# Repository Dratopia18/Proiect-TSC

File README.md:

# Proiect-TSC

# Diagrama Proiectului
<pre lang="markdown"> 
+-------------------------------------------+
|              POWER SECTION                |
|  +-------------+       +-----------------+|
|  | USB Type-C  |       | Charging Circuit||
|  | Connector   |------>| MCP73831        ||
|  | USB4110-GF-A|       | (Battery Mgmt)  ||
|  +-------------+       +-----------------+|
|         |                      |          |
|         v                      v          |
|  +-------------+       +-----------------+|
|  | USB to 3.3V |       | Battery Monitor ||
|  | XC6220A331MR|       | MAX17048G       ||
|  | (LDO Reg)   |       | (Fuel Gauge)    ||
|  +-------------+       +-----------------+|
|         |                                 |
+---------|---------------------------------+
          |
          v
+-----------------+        +-------------------+        +----------------+
| Interface       |        | Main Controller   |        | Memory         |
| +-------------+ |        | +---------------+ |        | +-----------+  |
| | microSD Card| |<------>| | ESP32-C6      | |<------>| | W25Q512J  |  |
| | Slot        | |        | | WROOM Module  | |        | | Flash     |  |
| +-------------+ |        | +---------------+ |        | | (64MB)    |  |
|                 |        |         |         |        |             |  |
| +-------------+ |        |         |         |        | +-----------+  |
| | FPC/FFC     | |<-------+         |         +------->| | DS3231    |  |
| | Connector   | |        |         |         |        | | RTC       |  |
| | (24-pin)    | |        |         v         |        | | w/Battery |  |
| +-------------+ |        | +---------------+ |        +----------------+
+-----------------+        | | Control Logic | |
                           | | Buttons       | |
                           | | (Reset/Boot)  | |
                           | +---------------+ |
                           +-------------------+
                                    |
                                    v
                           +-------------------+
                           | Peripherals       |
                           | +--------------+  |
                           | | BME680       |  |
                           | | Environment  |  |
                           | | Sensor (I2C) |  |
                           | +--------------+  |
                           |                   |
                           | +--------------+  |
                           | | QWIIC/I2C    |  |
                           | | Connector    |  |
                           | +--------------+  |
                           +-------------------+
</pre>

# Tabela BOM a proiectului
| Nr. | Componentă | Descriere | Furnizor | Link Achiziție | Datasheet |
|-----|------------|-----------|----------|----------------|-----------|
| 1 | ESP32-C6-WROOM-1-N8 | Microcontroller ESP32-C6 cu WiFi 6 și Bluetooth 5 | Digikey | https://www.digikey.com/en/products/detail/espressif-systems/ESP32-C6-WROOM-1-N8/17728866 | https://www.espressif.com/sites/default/files/documentation/esp32-c6-wroom-1_wroom-1u_datasheet_en.pdf |
| 2 | BME680 | Senzor integrat de mediu (temperatură, umiditate, presiune, gaz) | Digikey | https://www.digikey.com/en/products/detail/bosch-sensortec/BME680/7401317 | https://www.bosch-sensortec.com/media/boschsensortec/downloads/datasheets/bst-bme680-ds001.pdf |
| 3 | SD0805S020S1R0 | Diodă Schottky Barrier | Mouser | [https://www.mouser.com/ProductDetail/581-SD0805S020S1R0](https://ro.mouser.com/ProductDetail/KYOCERA-AVX/SD0805S020S1R0?qs=jCA%252BPfw4LHbpkAoSnwrdjw%3D%3D) | [http://datasheets.avx.com/schottky.pdf](https://ro.mouser.com/datasheet/2/40/schottky-3165252.pdf) |
| 4 | CPH3225A | Condensator 0.011F 3.3V 1210 | Digikey | https://www.digikey.com/en/products/detail/murata-electronics/CPH3225A/8692444 | [https://product.tdk.com/info/en/catalog/datasheets/mlcc_commercial_general_en.pdf](https://mm.digikey.com/Volume0/opasdata/d220001/medias/docus/6537/rev05-CPHCPM.pdf) |
| 5 | XC6220A331MR_G | Regulator de tensiune LDO | Digikey | https://www.digikey.com/en/products/detail/torex-semiconductor-ltd/XC6220A331MR-G/10165775 | https://www.torexsemi.com/file/xc6220/XC6220.pdf |
| 6 | SI1308EDL_T1_GE3 | Tranzistor MOSFET N-Channel | Digikey | https://www.digikey.com/en/products/detail/vishay-siliconix/SI1308EDL-T1-GE3/4876435 | https://www.vishay.com/docs/68734/si1308edl.pdf |
| 7 | CSR0402JTR470 | Rezistor 47 Ohm 0402 | Digikey | https://www.digikey.com/en/products/detail/stackpole-electronics-inc/CSR0402JTR470/6270526 | https://www.seielect.com/catalog/sei-rmcf_rmcp.pdf |
| 8 | KMS231GPLFS | Switch tactil | Mouser | [https://www.mouser.com/ProductDetail/611-KMS231GPLFS](https://ro.mouser.com/ProductDetail/CK/KMS231GP-LFS?qs=Qe4e1uPWiB2lCKabCZjjQg%3D%3D) | https://www.ckswitches.com/media/1464/kms.pdf |
| 9 | PGB1010603MR | Diodă de protecție ESD | Digikey | https://www.digikey.com/en/products/detail/littelfuse-inc/PGB1010603MR/715755 | https://www.littelfuse.com/~/media/electronics/datasheets/polymer_esd_suppressors/littelfuse_polymer_esd_suppressor_pgb_datasheet.pdf |
| 10 | CC0805KKX7R9BB105 | Condensator ceramic 1μF 50V | Digikey | https://www.digikey.com/en/products/detail/yageo/CC0805KKX7R9BB105/5195292 | https://www.yageo.com/upload/media/product/productsearch/datasheet/mlcc/UPY-GPHC_X7R_6.3V-to-50V_18.pdf |
| 11 | C1206C105K5RAC | Condensator ceramic 1μF 50V 1206 | Mouser | [https://www.mouser.com/ProductDetail/80-C1206C105K5R](https://ro.mouser.com/ProductDetail/KEMET/C1206C105K5RAC?qs=NTAB53G5bVDYFBtoIe7UwQ%3D%3D) | https://www.yageo.com/upload/media/product/productsearch/datasheet/mlcc/UPY-GPHC_X7R_6.3V-to-50V_18.pdf |
| 12 | C0402C105Z9VACTU | Condensator ceramic 1μF 10V 0402 | Mouser | [https://www.mouser.com/ProductDetail/80-C0402C105Z9VAC](https://ro.mouser.com/ProductDetail/KEMET/C0402C105Z9VACTU?qs=gt1LBUVyoHlQieoJt4iw1w%3D%3D) | https://www.yageo.com/upload/media/product/productsearch/datasheet/mlcc/UPY-GPHC_X5R_4V-to-50V_25.pdf |
| 13 | TAJB107K010RNJ | Condensator tantalum 100μF 10V | Digikey | https://www.digikey.com/en/products/detail/kyocera-avx/TAJB107K010RNJ/9748493 | https://componentsearchengine.com/Datasheets/1/TAJB107K010RNJ.pdf |
| 14 | C0402C475M9PACTU | Condensator ceramic 4.7μF 6.3V 0402 | Mouser | [https://www.mouser.com/ProductDetail/80-C0402C475M9PAC](https://ro.mouser.com/ProductDetail/KEMET/C0402C475M9PACTU?qs=x4XeXhDQKnr0GX0Xu9DUoQ%3D%3D) | https://www.yageo.com/upload/media/product/productsearch/datasheet/mlcc/UPY-GPHC_Y5V_6.3V-to-50V_20.pdf |
| 15 | DMG2305UX_7 | Tranzistor MOSFET P-Channel | Digikey | https://www.digikey.com/en/products/detail/diodes-incorporated/DMG2305UX-7/4340667 | https://www.diodes.com/assets/Datasheets/DMG2305UX.pdf |
| 16 | WCR0402-100KFA | Rezistor 100k Ohm 0402 | Mouser | [https://www.mouser.com/ProductDetail/652-WCR0402-100KFA](https://ro.mouser.com/ProductDetail/Welwyn-Components-TT-Electronics/WCR0402-100KFA?qs=%2F5Ar%2FAxv93DcWIrqMX6zjw%3D%3D) | https://www.welwyn-tt.com/wp-content/uploads/2020/07/Welwyn_WCR_Series_-_Issue_5_-_April_2020.pdf |
| 17 | PFMF.050.2 | Siguranță PTC resetabilă | Mouser | [https://www.mouser.com/ProductDetail/652-PFMF.050.2](https://ro.mouser.com/ProductDetail/Schurter/PFMF.050.2?qs=1auRipcfynCums5v1iucSA%3D%3D) | https://www.littelfuse.com/~/media/electronics/datasheets/resettable_ptcs/littelfuse_ptc_pfmf_datasheet.pdf |
| 18 | 744043680 | Inductor de putere 68μH | Mouser | [https://www.mouser.com/ProductDetail/710-744043680](https://ro.mouser.com/ProductDetail/Wurth-Elektronik/744043680?qs=PGXP4M47uW6VkZq%252BkzjrHA%3D%3D) | https://www.we-online.com/components/products/datasheet/744043680.pdf |
| 19 | MBR0530T3G | Diodă Schottky 0.5A 30V | Mouser | [https://www.mouser.com/ProductDetail/863-MBR0530T3G](https://ro.mouser.com/ProductDetail/onsemi/MBR0530T3G?qs=3JMERSakebpEmdUS6GetdQ%3D%3D) | https://www.onsemi.com/pdf/datasheet/mbr0530t1-d.pdf |
| 20 | SM04B_SRSS_TB | Conector JST SH 4 pini SMD | Digikey | https://www.digikey.com/en/products/detail/jst-sales-america-inc/SM04B-SRSS-TB-LF-SN/926710 | https://www.jst-mfg.com/product/pdf/eng/eSH.pdf |
| 21 | MAX17048G_T10 | Monitor de baterie Li+ | Digikey | https://www.digikey.com/en/products/detail/analog-devices-inc-maxim-integrated/MAX17048G-T10/3758921 | https://datasheets.maximintegrated.com/en/ds/MAX17048-MAX17049.pdf |
| 22 | MCP73831T_2ACI_OT | Controller de încărcare Li-Ion/Li-Polymer | Digikey | https://www.digikey.com/en/products/detail/microchip-technology/MCP73831T-2ACI-OT/964301 | https://ww1.microchip.com/downloads/en/DeviceDoc/MCP73831-Family-Data-Sheet-DS20001984H.pdf |
| 23 | BD5229G-TR | Detector de tensiune cu timp de întârziere ajustabil | Digikey | https://www.digikey.com/en/products/detail/rohm-semiconductor/BD5229G-TR/658502 | https://fscdn.rohm.com/en/products/databook/datasheet/ic/power/voltage_detector/bd52xxg-e.pdf |
| 24 | DS3231SN# | RTC (Real Time Clock) Serial | Digikey | https://www.digikey.com/en/products/detail/analog-devices-inc-maxim-integrated/DS3231SN/1197576 | https://datasheets.maximintegrated.com/en/ds/DS3231.pdf |
| 25 | W25Q512JVEIQ | Memorie Flash SPI 512Mbit | Digikey | https://www.digikey.com/en/products/detail/winbond-electronics/W25Q512JVEIQ/10244706 | https://www.winbond.com/resource-files/w25q512jv%20revf%2010142020%20plus.pdf |
| 26 | FH34SRJ-24S-0.5SH(99) | Conector FPC 24 pini | Mouser | [https://www.mouser.com/ProductDetail/798-FH34SRJ24S05SH99](https://ro.mouser.com/ProductDetail/Hirose-Connector/FH34SRJ-24S-0.5SH99?qs=vcbW%252B4%252BSTIpKBl5ap9J8Fw%3D%3D) | https://www.hirose.com/product/document?clcode=CL0570-0597-0-00&productname=FH34SRJ-24S-0.5SH(99)&series=FH34&documenttype=Catalog&lang=en&documentid=D31688_en |
| 27 | C0402C104K4RACTU | Condensator ceramic 0.1μF 16V 0402 | Digikey | https://www.digikey.com/en/products/detail/kyocera-avx/C0402C104K4RACTU/789653 | https://ds.yuden.co.jp/TYCOMPAS/ut/download?pn=CC0402JRNPO9BN220&fileType=CA |
| 28 | USBLC6-2SC6Y | Circuit de protecție ESD pentru USB | Digikey | https://www.digikey.com/en/products/detail/stmicroelectronics/USBLC6-2SC6Y/2819177 | https://www.st.com/resource/en/datasheet/usblc6-2.pdf |
| 29 | USB4110-GF-A | Conector USB Type-C | Digikey | https://www.digikey.com/en/products/detail/gct/USB4110-GF-A/10384547 | https://gct.co/connector/usb4110 |
| 30 | 112A-TAAR-R03 | Conector pentru antenă | Digikey | https://www.digikey.com/en/products/detail/linx-technologies-inc/112A-TAAR-R03/17633923 | https://linxtechnologies.com/wp/wp-content/uploads/112-series-data-sheet.pdf |

# Descrierea Funcționalității Hardware

## Modulul Microcontroller

Proiectul este bazat pe modulul ESP32-C6-WROOM-1-N8, un microcontroller de ultimă generație care include WiFi 6 și Bluetooth 5. Acest modul oferă performanțe excelente și un consum de energie redus, fiind ideal 
pentru aplicații IoT.

## Senzori

BME680 - un senzor integrat de mediu produs de Bosch Sensortec care măsoară:

* Temperatura (între -40°C și +85°C)
* Umiditatea relativă (între 0% și 100%)
* Presiunea barometrică (între 300hPa și 1100hPa)
* Calitatea aerului (prin măsurarea compușilor organici volatili)

Senzorul se conectează la ESP32-C6 prin interfața I2C, utilizând pinii SDA și SCL.

DS3231SN - un Real Time Clock (RTC) de înaltă precizie:

* Menține data și ora precisă
* Include compensare de temperatură
* Interfațare prin I2C
* Backup cu baterie pentru păstrarea timpului când alimentarea principală este întreruptă

## Sistemul de Alimentare

Încărcător de baterie Li-Ion/Li-Polymer:

* Controller dedicat MCP73831T-2ACI-OT
* LED indicator pentru starea încărcării
* Circuite de protecție pentru baterie

Management Energie:

* Regulator LDO XC6220A331MR_G pentru alimentare stabilă 3.3V
* Detector de tensiune BD5229G-TR pentru monitorizarea nivelului bateriei
* Monitor de baterie MAX17048G_T10 pentru măsurarea precisă a nivelului de încărcare
* Circuite de protecție PTC (PFMF.050.2) pentru protecție la supracurent

Convertoare DC-DC:
* Inductori de putere (744043680) pentru conversia eficientă a tensiunii
* Diode Schottky (SD0805S020S1R0, MBR0530T3G) pentru circuitele de comutație

## Stocare
Sistemul include memoria flash W25Q512JVEIQ de 512Mbit (64MB) conectată prin interfața SPI, oferind:

* Spațiu amplu pentru logging de date
* Viteză mare de citire/scriere (până la 104 MHz în mod SPI)
* Suport pentru modul Quad SPI pentru transfer de date accelerat
* Durată de retenție a datelor de peste 20 de ani

## Conectivitate

USB Type-C:

* Conector USB4110-GF-A pentru încărcare și comunicare
* Circuit de protecție USBLC6-2SC6Y pentru protecție ESD
* Suport pentru comunicare serială prin UART

Interfață FPC:

* Conector FH34SRJ-24S-0.5SH(99) cu 24 de pini
* Permite conectarea modulelor de expansiune sau a ecranelor
* Accesează multiple interfețe (I2C, SPI, GPIO)

Conectivitate Wireless:

* WiFi 6 integrat în modulul ESP32-C6
* Bluetooth 5.0 pentru conectivitate la dispozitive mobile
* Conector pentru antenă externă 112A-TAAR-R03 pentru îmbunătățirea recepției

## Interfața Utilizator

Butoane Tactile:

* Buton de boot (KMS231GPLFS) pentru intrarea în modul de programare
* Buton de reset (KMS231GPLFS) pentru repornirea sistemului
* Butoane adiționale configurabile de utilizator

LED-uri de Status:

* LED pentru indicarea stării de încărcare
* LED pentru indicarea activității sistemului
* LED-uri configurabile pentru notificări personalizate

# Pinii ESP32-C6: Functia si utilizarea fiecarui pin

| Pin     | Funcție        | Modul de utilizare                                               |
|---------|----------------|------------------------------------------------------------------|
| 3V3     | Supply         | Furnizează tensiune de 3.3V pentru componente.                   |
| GND     | Ground         | Referință pentru circuit.                                        |
| EN      | Enable         | Permite pornirea/resetarea modulului (tensiune ridicată = activ).|
| IO0     | INT_RTC (Interrupt)       | Pentru notificări, conectat la modulul RTC.                      |
| IO1     | RTC CLK        | Semnal de ceas pentru modulul RTC.                               |
| IO2     | SPI MISO       | Primire date de la periferice conectate prin SPI.                |
| IO3     | Status         | Semnalizează starea de ocupare a display-ului.                   |
| IO4     | Slave Select   | Selectează cardul SD.                                            |
| IO5     | Data/Command   | Selectează între modul de date și comenzi.                       |
| IO6     | SPI CLK        | Semnal de ceas pentru SPI.                                       |
| IO7     | SPI MOSI       | Transfer date către periferice conectate prin SPI.               |
| IO8     | GPIO           | Pin general GPIO.                                                |
| IO9     | IO/BOOT           | Conectat la un buton pentru intrarea în modul de boot.           |
| IO10    | EPD_CS  (Chip Select)    | Activează comunicarea cu display-ul.                             |
| IO11    | FLASH_CS (Chip Select)    | Activează comunicarea cu memoria flash.                          |
| IO12    | USB_D-         | Pentru USB.                                                      |
| IO13    | USB_D+         | Pentru USB.                                                      |
| IO15    | IO/CHANGE         | Conectat la un buton.                                            |
| IO16    | TX             | Pentru UART.                                                     |
| IO17    | RX             | Pentru UART.                                                     |
| IO18    | RTC_RST        | Pentru resetarea modulului RTC.                                  |
| IO19    | I2C_PW         | Supply pentru I2C.                                               |
| IO20    | EPD_3V3_C      | Alimentare display.                                              |
| IO21    | SDA            | Linia de date pentru I2C.                                        |
| IO22    | SCL            | Semnalul de ceas pentru I2C.                                     |
| IO23    | EPD_RST        | Pentru resetarea display-ului.                                   |

## Calcule de Consum Energetic

Consumul în diferite moduri de operare:

Mod Activ (Toate funcțiile active):

* ESP32-C6: ~60mA @ 3.3V
* BME680: ~3.7mA în mod activ
* DS3231: ~0.15mA
* Memorie Flash: ~15mA în operație de scriere
* Monitor baterie: ~0.5mA
* Circuite adiționale: ~5mA

Total mod activ: ~84.35mA @ 3.3V = 278.35mW

Mod Normal (Funcționare tipică):

* ESP32-C6: ~35mA (WiFi activ, procesor la viteză medie)
* BME680: ~1mA (măsurători periodice)
* DS3231: ~0.15mA
* Memorie Flash: ~1mA (operații ocazionale)
* Circuite adiționale: ~3mA

Total mod normal: ~40.15mA @ 3.3V = 132.5mW

Mod Sleep (Economisire energie):

* ESP32-C6: ~10μA (deep sleep)
* BME680: ~0.15μA (sleep)
* DS3231: ~0.15mA (activ pentru menținerea timpului)
* Circuite adiționale: ~50μA

Total mod sleep: ~0.21mA @ 3.3V = 0.693mW

Durata de viață a bateriei:

Considerând o baterie Li-Po de 1200mAh:

* În mod activ: ~14.2 ore
* În mod normal: ~29.9 ore
* Cu ciclu de funcționare optimizat (10% mod normal, 90% mod sleep): ~8-10 zile

# Design PCB și Considerații Mecanice

Dimensiuni PCB:

* Dimensiuni totale: 80mm x 40mm
* Grosime PCB: 1 mm
* Straturi: 3 (Top, Dielectrical, Bottom)

Considerații Termice:

* Componentele cu disipare mare de căldură (regulatoare, încărcător baterie) plasate cu zone de disipare adecvate
* Vias termice sub ESP32-C6 pentru disiparea căldurii

Layout Componente:

* Secțiune RF (antenă WiFi/BT) izolată și optimizată pentru performanță
* Separarea circuitelor digitale de cele analogice pentru minimizarea interferențelor
* Componente sensibile la zgomot (senzori) plasate departe de surse de interferență
* Integrarea ESP32-C6 oferă capabilități WiFi 6 și Bluetooth de ultimă generație
* Senzorul BME680 permite monitorizarea completă a parametrilor de mediu
* Sistemul de management al energiei optimizat pentru durată lungă de funcționare
* Conectorul FPC permite extensibilitate și adăugarea de module viitoare

Perspective de dezvoltare:

* Adăugarea unui ecran E-Ink pentru afișare cu consum ultra-redus
* Implementarea unui încărcător solar pentru autonomie completă
* Dezvoltarea de module de expansiune specifice pentru diverse aplicații
* Optimizarea și mai pronunțată a consumului energetic pentru funcționare pe termen lung

Limitări actuale:

* Dimensiunile pot fi reduse în versiunile viitoare
* Costuri de producție pot fi optimizate prin reducerea numărului de componente
* Protecție IP limitată fără carcasă dedicată

# Concluzie
Proiectul actual reprezintă o platformă de dezvoltare IoT completă, bazată pe ESP32-C6, cu capabilități extinse de senzori, managementul energiei, și opțiuni de conectivitate. Design-ul hardware a fost realizat
cu accent pe eficiență energetică, flexibilitate și fiabilitate, permițând o gamă largă de aplicații de la monitorizarea mediului până la controlul automatizărilor.

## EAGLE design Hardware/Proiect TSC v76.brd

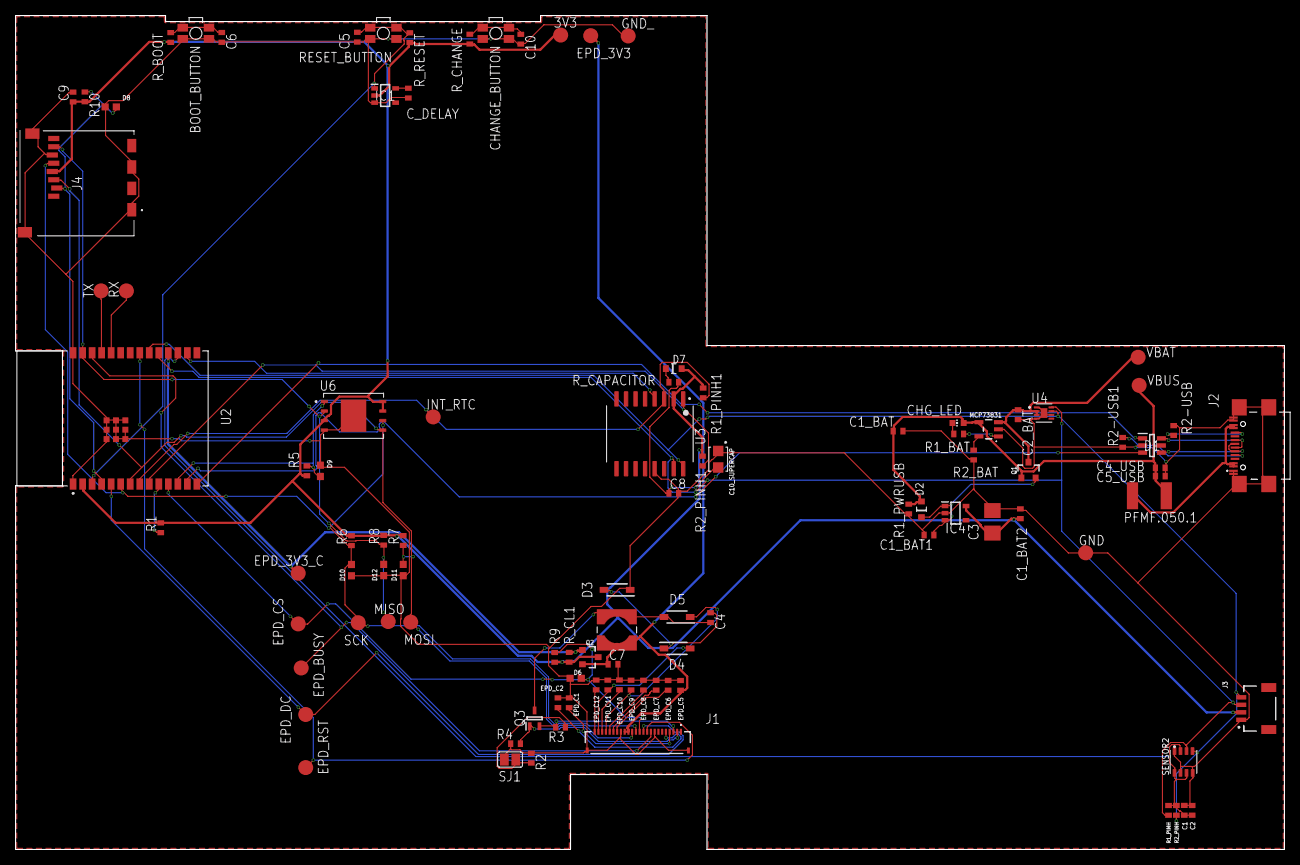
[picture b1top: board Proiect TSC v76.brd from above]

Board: 2 copper layers, 169.2 x 111.2 mm, 103 parts (0 on the bottom side), 55 nets.

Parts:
3V3: TPTP20R; TP20R
BOOT_BUTTON: BUTTON_CUSYOMV1; MYBUTTON
C1, C2, C4_USB, C5_USB, C9: 100nF; ESP32_WROVER_EAGLE-LTSPICE_C0402
C1_BAT, C1_BAT1, C1_BAT2, C2_BAT: 4.7uF; ESP32_WROVER_EAGLE-LTSPICE_C0402
C3: 100uF TANT; RCL_CT3528
C4: 4.7uF/25V; ESP32_WROVER_EAGLE-LTSPICE_C0402
C5: 1uF; EAGLE-LTSPICE_C0402
C6, C8, C10: 100nF; EAGLE-LTSPICE_C0402
C7: 10uF; EAGLE-LTSPICE_C0402
C10_SUPERCAP: CPH3225A; CAPCP3225X100N
CHANGE_BUTTON: BUTTON_CUSYOMV1; MYBUTTON
CHG_LED: ADAFRUIT_CHIP-LED0603
C_DELAY: 100nF; EAGLE-LTSPICE_C0402
D1: USBLC6-2SC6Y; SOT95P280X145-6N
D2, D7: ESP32_WROVER_AVX---SD0805S020S1R0_AVX_SD0805S020S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; ESP32_WROVER_AVX---SD0805S020S1R0_AVX_SD0805S020S1R0_0
D3, D4, D5: MBR0530; SOD3716X135N
D6, D8, D9, D10, D11, D12: PGB1010603MR; DIOC1608X36N
EPD_3V3, EPD_3V3_C: TPTP20R; TP20R
EPD_BUSY: TPTP20R; TP20R
EPD_C1, EPD_C2, EPD_C5, EPD_C6, EPD_C7, EPD_C8, EPD_C9, EPD_C10, EPD_C11, EPD_C12: 1uF/50V; ESP32_WROVER_EAGLE-LTSPICE_C0402
EPD_CS: TPTP20R; TP20R
EPD_DC: TPTP20R; TP20R
EPD_RST: TPTP20R; TP20R
GND: TPTP20R; TP20R
GND_: TPTP20R; TP20R
IC1: BD5229G-TR; SOT95P280X125-5N
IC4: XC6220A331MR-G; SOT95P280X120-5N
INT_RTC: TPTP20R; TP20R
J1: FH34SRJ-24S-0.5SH_99_; FH34SRJ24S05SH99
J2: SAMACSYS_PARTS_USB4110-GF-A; SAMACSYS_PARTS_USB4110GFA
J3: QWIIC_RIGHT_ANGLE; JST04_1MM_RA
J4: 112A-TAAR-R03_ATTEND; 112ATAARR03ATTEND
L1: 68uH; IND_4828-WE-TPC_WRE
MCP73831: ESP32_WROVER_SPARKFUN-IC-POWER_MCP73831; ESP32_WROVER_SPARKFUN-IC-POWER_SOT23-5
MISO: TPTP20R; TP20R
MOSI: TPTP20R; TP20R
PFMF.050.1: ESP32C6_VARISTORCN1812; ESP32C6_VARISTOR_CT/CN1812
Q1, Q2: 20V/4.2A/52mΩ/1.4W; ESP32_WROVER_SPARKFUN-DISCRETESEMI_SOT23-3
Q3: SI1308EDL-T1-GE3; SOT65P210X110-3N
R1, R1_PINH, R1_PINH1, R2_PINH, R2_PINH1, R5, R6, R7, R8, R9, R10: 10K; ESP32_WROVER_EAGLE-LTSPICE_R0402
R1_BAT: 200; ESP32_WROVER_EAGLE-LTSPICE_R0402
R1_PWRUSB: 100K; ESP32_WROVER_EAGLE-LTSPICE_R0402
R2: 2.2; ESP32_WROVER_EAGLE-LTSPICE_R0402
R2-USB, R2-USB1: 5k1; ESP32_WROVER_EAGLE-LTSPICE_R0402
R2_BAT: 2K; ESP32_WROVER_EAGLE-LTSPICE_R0402
R3: 0.47; ESP32_WROVER_EAGLE-LTSPICE_R0402
R4: 10k; ESP32_WROVER_EAGLE-LTSPICE_R0402
RESET_BUTTON: BUTTON_CUSYOMV1; MYBUTTON
RX: TPTP20R; TP20R
R_BOOT: 10K; ESP32_WROVER_EAGLE-LTSPICE_R0402
R_CAPACITOR: 15; ESP32_WROVER_EAGLE-LTSPICE_R0402
R_CHANGE: 10K; ESP32_WROVER_EAGLE-LTSPICE_R0402
R_CL1: 10K; ESP32_WROVER_EAGLE-LTSPICE_R0402
R_RESET: 10K; ESP32_WROVER_EAGLE-LTSPICE_R0402
SCK: TPTP20R; TP20R
SENSOR2: ESP32_WROVER_BME680_BME680; ESP32_WROVER_BME680_PSON80P300X300X100-8N
SJ1: SJ
TX: TPTP20R; TP20R
U2: ESP32-C6-WROOM-1-N8; XCVR_ESP32-C6-WROOM-1-N8
U3: DS3231SN#; SOIC127P1032X265-16N
U4: MAX17048G+T10; SON50P200X200X80-9N
U6: W25Q512JVEIQ; SON127P600X800X80-9N
VBAT: TPTP20R; TP20R
VBUS: TPTP20R; TP20R

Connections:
3V3: 3V3.TP, C1_BAT2.1, C3.+, C9.1, D7.2, IC1.2, IC4.5, J3.2, J4.P4, Q2.3, R1.2, R1_PINH1.2, R2_PINH1.2, R5.2, R6.2, R7.2, R8.2, R9.2, R10.2, R_BOOT.2, R_CHANGE.2, R_CL1.2, R_RESET.2, U2.2, U3.2, U6.3, U6.7, U6.8
32KHZ: R2_PINH1.1, U2.9, U3.1
BOOT: BOOT_BUTTON.3, BOOT_BUTTON.4, C6.1, R_BOOT.1
CHANGE: C10.1, CHANGE_BUTTON.3, CHANGE_BUTTON.4, R_CHANGE.1
DN: D1.4, J2.A7, J2.B7
DP: D1.6, J2.A6, J2.B6
EPD_3V3: C7.1, EPD_3V3.TP, EPD_C5.2, J1.15, J1.16, L1.2, Q2.2
EPD_3V3_C: EPD_3V3_C.TP, Q2.1, R_CL1.1, U2.18
EPD_BUSY: EPD_BUSY.TP, J1.9, U2.26
EPD_CS: D6.2, EPD_CS.TP, J1.12, R9.1, U2.11
EPD_DC: EPD_DC.TP, J1.11, U2.5
EPD_RST: EPD_RST.TP, J1.10, U2.21
FLASH_CS: D9.2, R5.1, U2.12, U6.1
GDR: J1.2, Q3.1, R4.2
GND: BOOT_BUTTON.1, BOOT_BUTTON.2, C1.2, C1_BAT.2, C1_BAT1.2, C1_BAT2.2, C2.2, C2_BAT.2, C3.-, C4_USB.2, C5.2, C5_USB.2, C6.2, C7.2, C8.2, C9.2, C10.2, C10_SUPERCAP.1, CHANGE_BUTTON.1, CHANGE_BUTTON.2, C_DELAY.2, D1.2, D3.1, D6.1, D8.1, D9.1, D10.1, D11.1, D12.1, EPD_C1.1, EPD_C2.1, EPD_C5.1, EPD_C6.1, EPD_C7.1, EPD_C8.1, EPD_C9.1, EPD_C10.1, EPD_C11.1, EPD_C12.1, GND.TP, GND_.TP, IC1.3, IC4.2, J1.8, J1.17, J1.MP1, J1.MP2, J2.A1, J2.A12, J2.B1, J2.B12, J2.MP1, J2.MP2, J2.MP3, J2.MP4, J3.1, J4.G1, J4.G2, J4.G3, J4.G4, J4.P6, MCP73831.2, R1_PWRUSB.1, R2.1, R2-USB.2, R2-USB1.1, R2_BAT.1, R4.1, RESET_BUTTON.1, RESET_BUTTON.2, SENSOR2.1, SENSOR2.5, SENSOR2.7, SJ1.1, U2.1, U2.28, U2.29_1, U2.29_2, U2.29_3, U2.29_4, U2.29_5, U2.29_6, U2.29_7, U2.29_8, U2.29_9, U3.13, U4.1, U4.4, U4.6, U4.9, U6.4, U6.9
GPIO8: R1.1, U2.10
I2C_PW: C1.1, C2.1, R1_PINH.2, R2_PINH.2, SENSOR2.2, SENSOR2.6, SENSOR2.8, U2.17
INT_RTC: INT_RTC.TP, R1_PINH1.1, U2.8, U3.3
MISO: D12.2, J4.P7, MISO.TP, R8.1, U2.27, U6.2
MOSI: D11.2, J1.14, J4.P3, MOSI.TP, R7.1, U2.7, U6.5
unnamed: J2.A5, R2-USB1.2
unnamed: J2.B5, R2-USB.1
unnamed: C_DELAY.1, IC1.5
unnamed: C1_BAT1.1, D2.1, IC4.1, IC4.3, Q1.2
unnamed: MCP73831.5, R2_BAT.2
unnamed: D7.1, R_CAPACITOR.1
unnamed: C4.1, D3.2, D4.1
unnamed: EPD_C12.2, J1.24
unnamed: MCP73831.1, R1_BAT.2
unnamed: CHG_LED.C, R1_BAT.1
unnamed: C8.1, C10_SUPERCAP.2, R_CAPACITOR.2
unnamed: EPD_C10.2, J1.22
unnamed: EPD_C8.2, J1.20
unnamed: EPD_C7.2, J1.19
unnamed: EPD_C6.2, J1.18
unnamed: EPD_C2.2, J1.5
unnamed: EPD_C1.2, J1.4
PREVGH: D5.1, EPD_C9.2, J1.21
PREVGL: D4.2, EPD_C11.2, J1.23
RESE: J1.3, Q3.2, R3.2
RESE': R2.2, R3.1, SJ1.2
RESET: C5.1, IC1.1, RESET_BUTTON.3, RESET_BUTTON.4, R_RESET.1, U2.3
RTC_RST: U2.16, U3.4
RX: RX.TP, U2.24
SCK: D10.2, J1.13, J4.P5, R6.1, SCK.TP, U2.6, U6.6
SCL: J3.4, R2_PINH.1, SENSOR2.4, U2.20, U3.16, U4.7
SDA: J3.3, R1_PINH.1, SENSOR2.3, U2.19, U3.15, U4.8
SRC: C4.2, D5.2, L1.1, Q3.3
SS_SD: D8.2, J4.P2, R10.1, U2.4
TX: TX.TP, U2.25
USB_D+: D1.1, U2.14
USB_D-: D1.3, U2.13
VBAT: C2_BAT.1, MCP73831.3, Q1.3, U4.2, U4.3, VBAT.TP
VBUS: C1_BAT.1, C4_USB.1, C5_USB.1, CHG_LED.A, D1.5, D2.2, MCP73831.4, PFMF.050.1.2, Q1.1, R1_PWRUSB.2, VBUS.TP
VUSB: J2.A4, J2.A9, J2.B4, J2.B9, PFMF.050.1.1

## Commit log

2025-04-05 upload proiect TSC (part 1)
2025-04-05 upload proiect TSC (part 2)
2025-04-05 Create LICENSE
2025-04-06 Upload proiect TSC (poze)
2025-04-13 Rezolvare Issue #6: Formatare necorespunzătoare a textului în README
    Am modificat README-ul, astfel incat acesta sa fie citet si coerent.
2025-04-13 Delete Hardware/Proiect_TSC_v48.sch
    Pentru rezolvarea primelor doua issueuri, trebuie sa stergem versiunea precedenta a fisierului schematic
2025-04-13 Rezolvare issue #1 si issue #2
    Am modificat fisierul schematic astfel incat acesta sa includa frameul standard (marit astfel incat sa incapa toate componentele din fisa schematica) si am facut si delimitare clara a blocurilor func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
2025-04-13 Delete Hardware/Proiect TSC v74.brd
    Pentru rezolvarea issuerilor #3, #4 si #5, trebuie stearsa versiunea veche a fisierului cu boardul
2025-04-13 Rezolvare la issuerile #3, #4 si #5
    In aceasta versiune modificata, am micsorat marcajele de la condensatorii FFC, astfel incat acesta sa fie lizibil, am schimbat numele testpadurilor, in asa fel incat sa aiba denumirea semnalelor core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
2025-04-13 Delete Mechanical directory
    Pentru issueul 7, suntem nevoiti sa inlocuim intregul folder Mechanical, cu o versiune imbunatatita, ce rezolva problema.
2025-04-13 Rezolvarea issueului #7
    Am modificat modelul tabletei OpenBook, astfel incat componentele PCB-ului sa fie redirectionate catre display si sa ne asiguram ca pozitionarea componentelor este una corecta.
2025-04-13 Delete Images directory
    Trebuie schimbate pozele ca sa rezolvam integral issueul #7
2025-04-13 Imagini noi pentru tableta OpenBook
2025-04-14 Re-rezolvare issue #6
    Am mai modificat putin readme-ul

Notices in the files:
parts and their libraries:
COPYRIGHT: Copyright (C) 2024 Ultra Librarian. All rights reserved.
